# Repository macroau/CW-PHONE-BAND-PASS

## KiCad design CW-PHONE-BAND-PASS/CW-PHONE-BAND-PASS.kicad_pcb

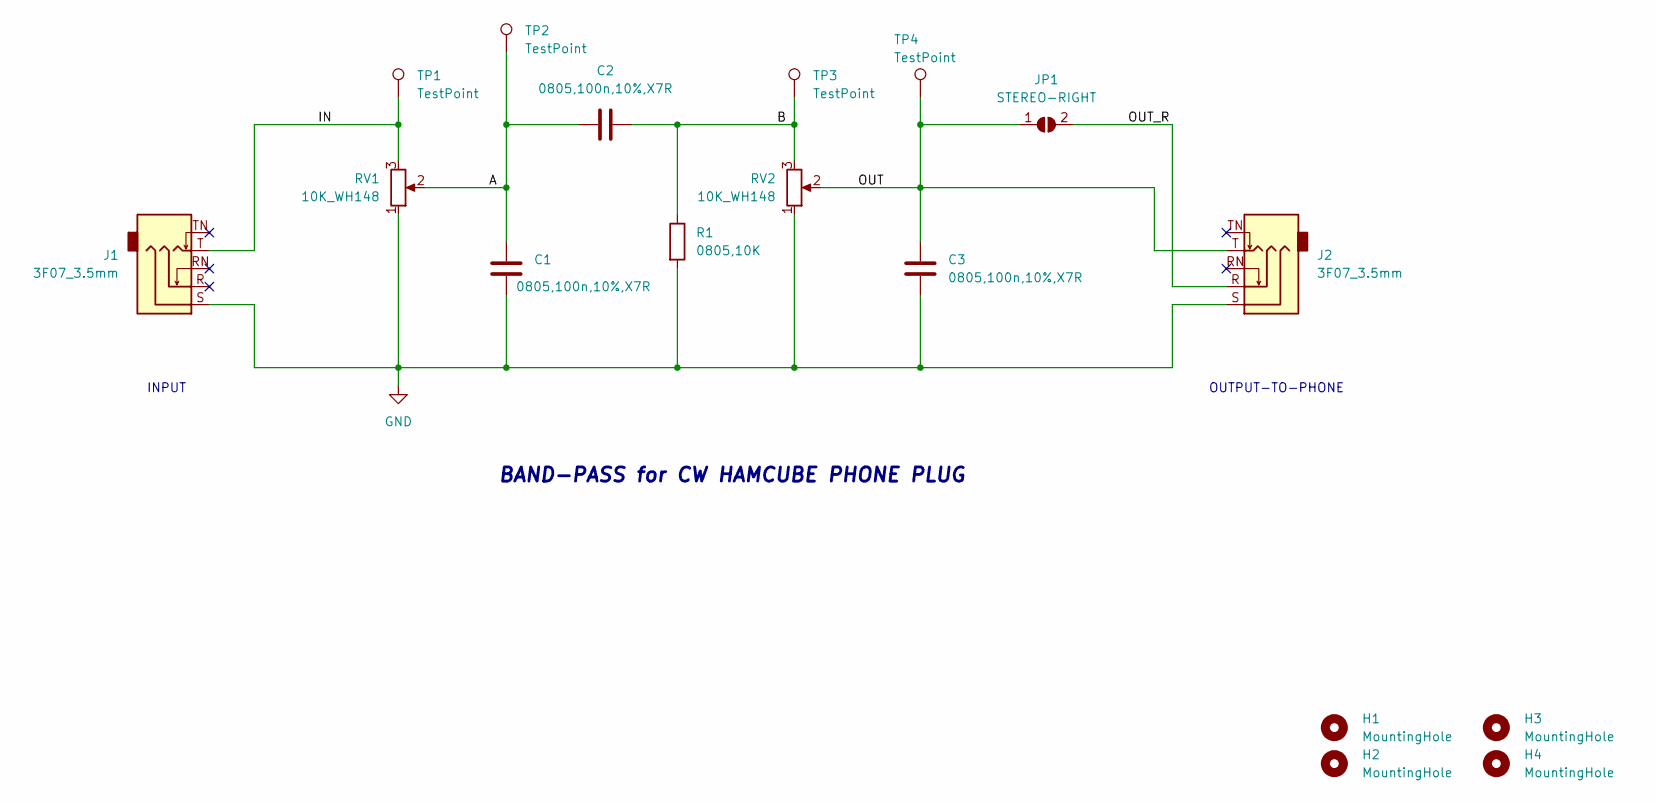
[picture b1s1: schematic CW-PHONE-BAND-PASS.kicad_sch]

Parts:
C1, C2, C3: 0805,100n,10%,X7R; C_0805_2012Metric_Pad1.18x1.45mm_HandSolder
H1, H2, H3, H4: MountingHole; MountingHole_2.7mm_M2.5
J1, J2: 3F07_3.5mm; AUDIOJACK_3F07_3.5
JP1: STEREO-RIGHT; SolderJumper-2_P1.3mm_Open_RoundedPad1.0x1.5mm
R1: 0805,10K; R_0805_2012Metric_Pad1.20x1.40mm_HandSolder
RV1, RV2: 10K_WH148; POT_SINGLE_WH148
TP1, TP2, TP3, TP4: TestPoint; TestPoint_THTPad_D1.0mm_Drill0.5mm

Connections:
/A: C1.1, C2.1, RV1.2, TP2.1
/B: C2.2, R1.1, RV2.3, TP3.1
/IN: J1.T, RV1.3, TP1.1
/OUT: C3.2, J2.T, JP1.1 (A), RV2.2, TP4.1
/OUT_R: J2.R, JP1.2 (B)
GND: C1.2, C3.1, J1.S, J2.S, R1.2, RV1.1, RV2.1

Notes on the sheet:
INPUT
BAND-PASS for CW HAMCUBE PHONE PLUG
OUTPUT-TO-PHONE

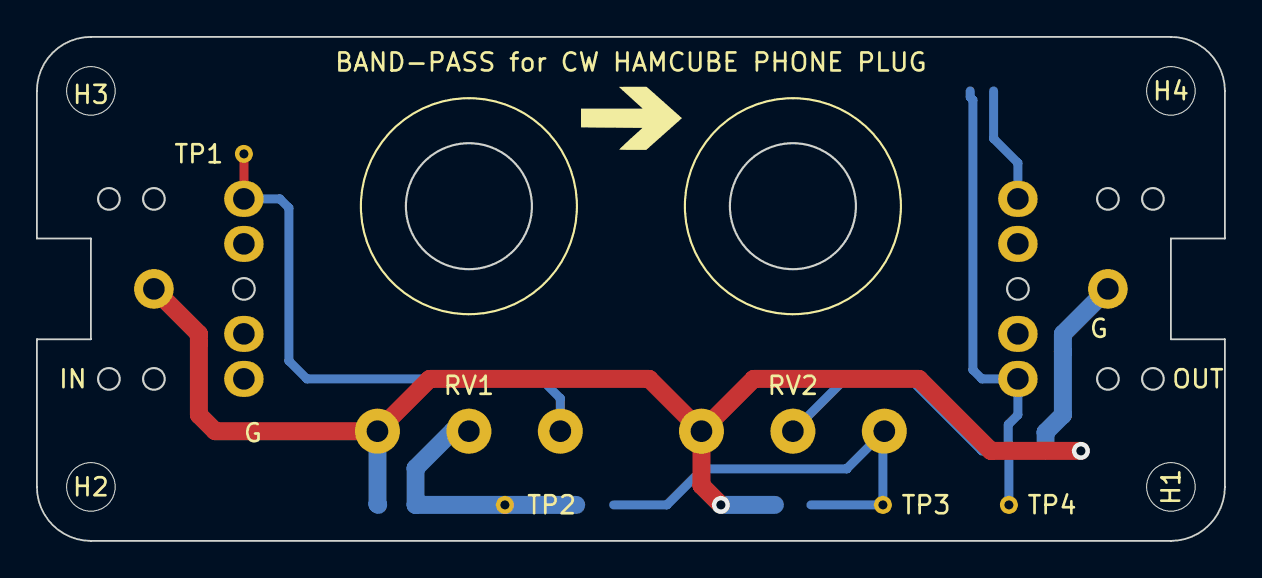
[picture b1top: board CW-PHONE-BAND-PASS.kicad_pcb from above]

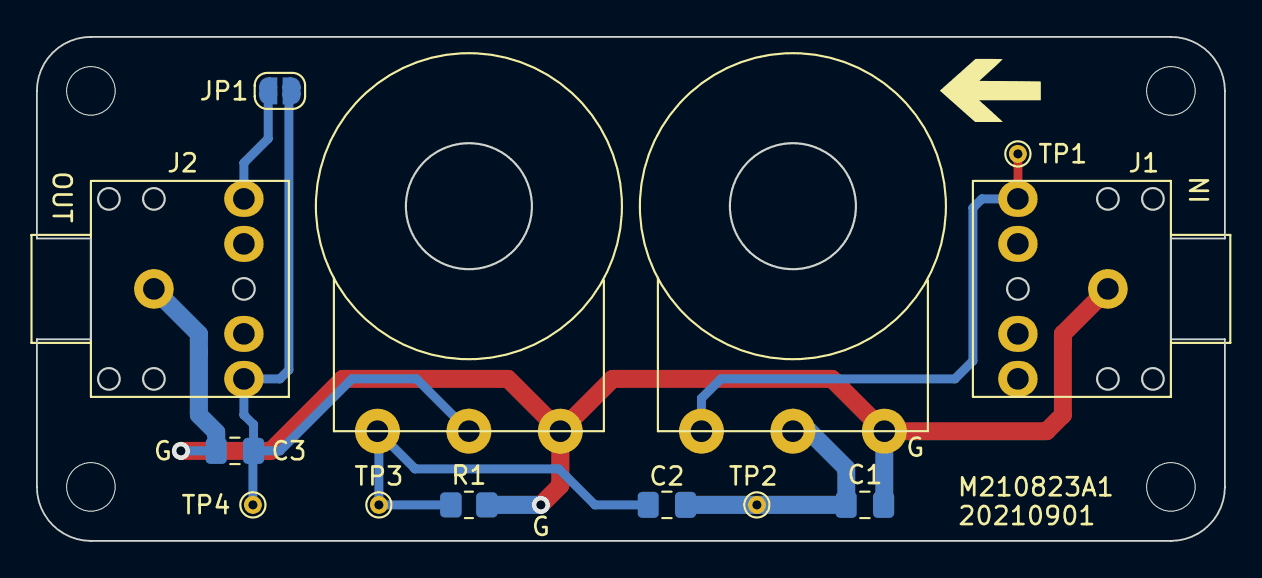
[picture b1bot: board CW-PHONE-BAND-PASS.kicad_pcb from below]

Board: 2 copper layers, 66.0 x 28.0 mm, 17 parts (11 on the bottom side), 6 nets.

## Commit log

2021-08-21 KiCAD files adn LTSpice files added.
    Changes to be committed:
    modified: .gitignore
    new file: CW-PHONE-BAND-PASS/CW-PHONE-BAND-PASS.kicad_pcb
    new file: CW-PHONE-BAND-PASS/CW-PHONE-BAND-PASS.kicad_prl
    new file: CW-PHONE-BAND-PASS/CW-PHONE-BAND-PASS.kicad_pro
    new file: CW-PHONE-BAND-PASS/CW-PHONE-BAND-PASS.kicad_sch
2021-08-27 first PCB version released. Gerbers generated.
2021-09-01 pcb updated. gerber files rev 1 generated.
